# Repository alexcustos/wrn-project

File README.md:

# WRN Project

WRN is 3-in-1 device for RS232 serial port was designed to solve some standard problems of a home server.

## The board based on the ATmega328P and consist of:

* The hardware watchdog timer
* True random number generator (based on avalanche noise)
* Low power 2.4GHz transceiver (nRF24L01+)

## The project consist of the following components:

* The schematic and the PCB (KiCAD project)
* The firmware (AtmelStudio project)
* Linux daemon, watchdog driver and the installation for the Gentoo (Makefile)

The project depends on:
* [alexcustos/RF24](https://github.com/alexcustos/RF24)
* [alexcustos/RF24Network](https://github.com/alexcustos/RF24Network)

Here's an article in russian with more details:
* [Part 1](https://geektimes.ru/post/275912/)
* [Part 2](https://habrahabr.ru/post/300968/)

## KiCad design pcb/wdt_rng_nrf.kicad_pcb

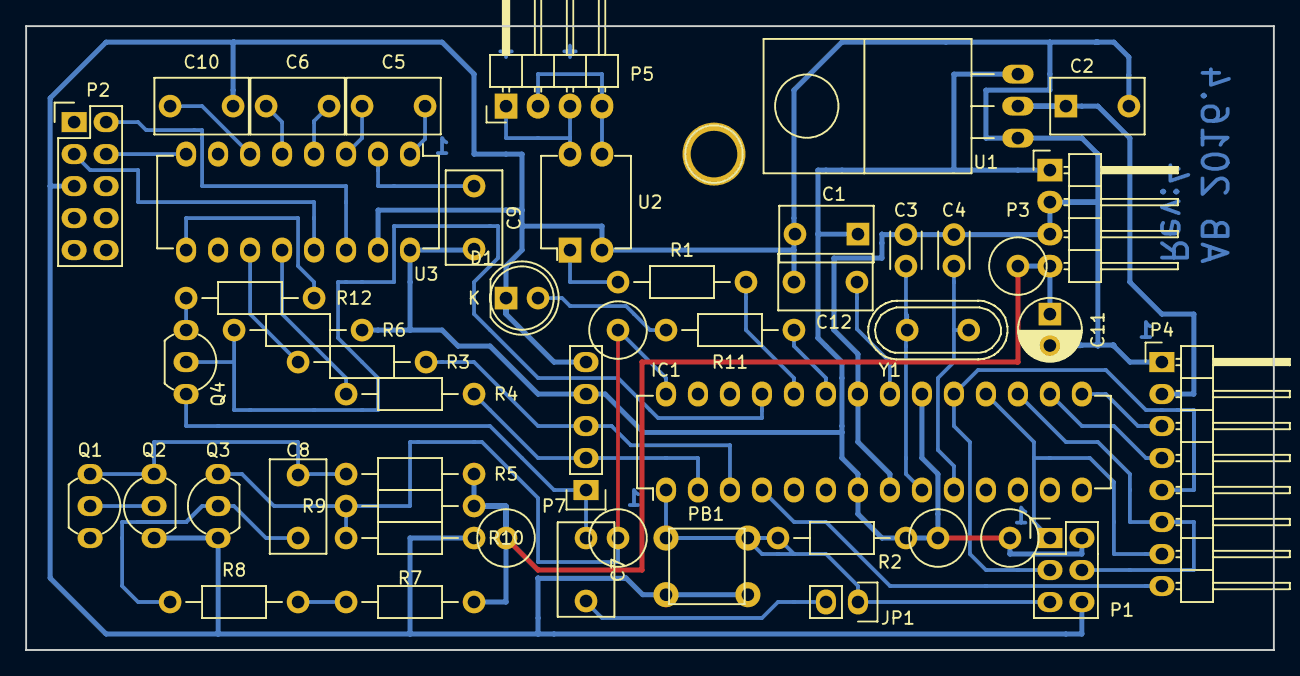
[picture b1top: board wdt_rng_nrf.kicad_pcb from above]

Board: 2 copper layers, 99.1 x 49.5 mm, 42 parts (0 on the bottom side), 43 nets.

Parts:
C1, C2: 10μF(tant); C_Disc_D7.5_P5
C3, C4: 22pF; C_Disc_D3_P2.5
C5, C6, C7, C8, C9, C10, C12: 0.1μF; C_Disc_D7.5_P5
C11: 10μF; C_Radial_D5_L6_P2.5
D1: LED; LED-5MM
IC1: ATMEGA328P-PU; DIP-28_W7.62mm
JP1: DTR; Pin_Header_Straight_1x02
P1: ICSP; Pin_Header_Straight_2x03
P2: RS232; Pin_Header_Straight_2x05
P3: FDD_PRW; Pin_Header_Angled_1x04
P4: nRF24L01+; Pin_Header_Angled_1x08
P5: SWITCH; Pin_Header_Angled_1x04
P7: FTDI; Pin_Header_Straight_1x05
PB1: RESET; Push_E-Switch_TC-0102
Q1, Q2, Q3: 2N3904; TO-92_2N3904
Q4: 2N7000; TO-92_2N7000
R1: 180Ω; Resistor_Horizontal_RM10mm
R2, R9: 10k; Resistor_Horizontal_RM10mm
R3, R4, R12: 1k; Resistor_Horizontal_RM10mm
R5: 4.7k; Resistor_Horizontal_RM10mm
R6: 1M; Resistor_Horizontal_RM10mm
R7: 820k; Resistor_Horizontal_RM10mm
R8: 680k; Resistor_Horizontal_RM10mm
R10: 6.8k; Resistor_Horizontal_RM10mm
R11: 470Ω; Resistor_Horizontal_RM10mm
U1: LM1117T-3.3; TO-220_Neutral123_Horizontal
U2: PC817; DIP-4_W7.62mm
U3: ADM202EANZ; DIP-16_W7.62mm
Y1: 20MHz; Crystal_HC49-U_Vertical

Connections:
CE: IC1.15, P4.3
CSN: IC1.16, P4.4
DTR: C7.1, P7.1, Q4.1
GND: C1.2, C2.2, C3.2, C4.2, C10.2, C11.2, C12.1, D1.1, IC1.8, IC1.22, P1.6, P2.5, P3.2, P3.3, P4.1, P7.5, PB1.3, PB1.4, Q2.3, Q3.3, R10.1, U1.1, U2.2, U3.15
IRQ: IC1.4, P4.8
MB_GND: P5.2, P5.4, U2.3
MISO: IC1.18, P1.1, P4.7
MOSI: IC1.17, P1.4, P4.6
NLOCK: IC1.25, Q4.2, R6.1
unnamed: C3.1, IC1.9, Y1.2
unnamed: C4.1, IC1.10, Y1.1
unnamed: C5.1, U3.3
unnamed: C5.2, U3.1
unnamed: C6.1, U3.5
unnamed: C6.2, U3.4
unnamed: C7.2, JP1.2
unnamed: C8.1, Q3.2, R8.1
unnamed: C8.2, Q1.3, Q2.1, R5.2
unnamed: C9.1, U3.2
unnamed: C10.1, U3.6
unnamed: C12.2, IC1.21
unnamed: D1.2, R11.1
unnamed: IC1.23, R11.2
unnamed: Q1.2, Q2.2
unnamed: Q4.3, R12.1
unnamed: R1.1, U2.1
unnamed: R3.1, U3.11
unnamed: R4.1, U3.12
unnamed: R7.1, R8.2
unnamed: R12.2, U3.9
RESET: IC1.1, JP1.1, P1.5, PB1.1, PB1.2, R2.2
RNG: IC1.28, Q3.1, R9.1, R10.2
RST_SW: P5.1, P5.3, U2.4
RS_DTR: P2.4, U3.8
RS_RX: P2.2, U3.14
RS_TX: P2.3, U3.13
RX: IC1.2, P7.2, R4.2
SCK: IC1.19, P1.3, P4.5
TX: IC1.3, P7.3, R3.2
VCC3.3V: C2.1, P4.2, U1.2
VCC5V: C1.1, C9.2, IC1.7, IC1.20, P1.2, P3.1, P7.4, R2.1, R6.2, U1.3, U3.16
VCC12V: C11.1, P3.4, R5.1, R7.2, R9.2
WDT_RST: IC1.24, R1.2

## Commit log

2016-05-19 Release v0.1
2016-05-19 Fixed: .hex binary files added
2016-05-19 Fixed: article links in the README.md
2016-05-20 Added: WDT fifo to make the driver useless
2016-05-21 Added: options for watchdog via wdt.fifo
2016-05-24 Optimized: reduce WDT update cycle (RNG speed up from 636 to 908 Bytes/s)
2016-05-25 Added: more CPU time to RNG; Adjusted: acceptable range
2016-05-25 Fixed: the serial port open flags
